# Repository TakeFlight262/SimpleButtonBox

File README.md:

# Simple Button Box

A simple button box, designed for my simracing rig. Includes 9 mechanical key switches and 2 3-way toggle switches.

I've wanted to have a button box for extra inputs on my simracing rig for awhile, so I finally made one!

The box uses 9 mechanical key switches (blue Cherry MX keys) so they feel tactile and satisfying. I also included two three-way toggle switches for additional inputs, totaling to about 13 inputs in total. While it's not a crazy amount, it's enough. The entire box is powered by an Arduino Pro Micro with a USB-C cable connection, making it easy to connect to (instead of micro-USB). I made this project so I could have something useful, but it's also a first for me. I started with a simple project to get the hang of designing projects like this from scratch, so that in the future I can build more complex things (maybe another button box!).
I designed the box to be clean and generic, not to flashy, so it'd fit with any rig and work with any car. I left enough space between buttons for labels and such, but made the buttons big enough so it's easy to press even with gloves in a rig! The buttons being tactile also helps when driving, when you need a sharp, tactile response from the button so you know how many inputs you've pressed.

Features:

* 9x Cherry MX Mechanical Key switches with custom 3D-printed keycaps
* 2x metal 3-way toggle switches (ON-OFF-ON)
* USB-C cable connection
* Removable top cover (for customization, painting, or fixing internal components etc.)
* Horizontal or vertical configuration

Assembly:

The front case is a press fit, and it should have a tight enough tolerance to stay on. If not, you might have to try changing print settings, adding magnets, or gluing (unfortunately). I may add magnets in the future if I find that the friction fit doesn't work well.

For the front cover, you'll notice I have a carbon fiber weave pattern. I printed the front cover on a carbon-fiber weave texture PEI build plate, but you can also wrap it, paint it, or leave it bare if you can't make or don't want the texture.

Buttons are press fit onto the key switches, like normal key caps.

I used mill-max hotswaps, and designed the PCB with that in mind. Solder those on, then add the key switches on top. Ensure that the hotswaps are flush with the board!

Arduino Pro Micro slides in on the BOTTOM, upside down (see above).

Diodes MUST face away from button and towards the row wires, otherwise the matrix will not work.

Switches share ground and solder to pins 9, 10, 14, 15. Change the code if you want to change the input.

If you're printing out the PCB using a 3D printer and soldering + hot gluing the components on like I did, use these wiring diagrams to wire everything up with (ideally) insulated wires. Drill holes to go front/back as needed (I used a solder and burned two holes through, for the row and column wires).

If you're printing/using the PCB:

For soldering order, I soldered the Arduino Pro Micro, then the diodes, then the hotswaps. Then add wires (if you're not using a PCB).

NOTE!!: If you're using the plastic PCB file, you have to be careful about soldering! I solder at 350-400 degrees, the plastic (PLA) will melt almost immediately upon contact with the iron. In order to solder, heat up the METAL component, add solder, then pull away the soldering iron relatively quickly It may take a few tries.

Once everything is soldered, you can slide the PCB onto the mounting pegs in the bottom case. You can add hot glue, superglue, or whatever you need. Just make sure to secure the board.

For the toggle switches, take off the hex nut and washer, slide the switch through the hole, screw on the hex nut and washer (washer on bottom), then turn the switch body while holding the hex nut> Or use a wrench to secure the hex nut. You can do this either vertically or horizontally, depending on how you want to mount the box (so the switches should always be up, but relative to the short side of the box). I mounted the box vertically, so the switches pointed towards/away from the buttons. You can also do it perpendicular (horizontal button box mounting). 

Once the toggle switches are on the lid, solder them to the PCB board.

I mentioned earlier that the lid is press fit. I ended up finding that that did not work! So I drilled two holes on either end. I drove a M2.5 x 8 screw in. It should be a pretty snug fit for the screw. It required a bit of force to screw in. If you want to use magnets or something else, screws are not necessary, but I 100% recommend them.

I also added hot glue around the PCB supports, just to make sure that those fragile supports don't bend or snap when unplugging/plugging the USB-C cable. But again, optional. 

If you find that the buttons don't spring back up, take a pen spring or similar sized springs, use pliers to expand their diameter, then slide them over the 3D printed buttons. I found that it made the buttons feel squishy, so I didn't end up using them> but if you like the added stiffness, then add them. It also might work better with a proper PCB, so I think that is important to note as well.

VERY IMPORTANT: Please be careful when gluing the PCB in, because the USB-C cable might not be able to reach inside if you do it wrong!!

Also note that I did not secure the PCB board, finding that it was ok, but you might need to. The electrical tape I put on the toggle switches ended up being stiff enough to push the board into place, so i found it to be ok. But again, you might need it.

I also found that if the switches are tilted at all and the buttons rub against the lid, you can hold the switch in place until it's straight, then add hot glue to secure it. But again, not sure if you'll need that with a regular PCB.

One FINAL thing: I printed the lid at 100.5%, so I'd recommend doing that, though slightly lower might be ok (my XY compensation was about -2.5mm, so take that into account).

Ok that's all, thanks for reading!

Firmware:

Check "External" folder for libraries, it's important.

Open Arduino IDE, open the sketch, then go to "Sketch>Include Library>Add .ZIP Library" and add the Joystick library.
Select "Tools>Board>Arduino AVR Boards>Arduino Leonardo"
Make sure you select the right COM port, then compile and upload.

If it doesn't upload (like it did for me), try double-clicking reset on the board (or connecting GND and RST twice quickly) right before Arduino IDE uploads.

Credits:

Claude gave me advice for writing firmware
Claude also wrote an upload file to fix an issue on my computer where Arduino wasn't uploading the sketch. I originally included the file in the repo but removed it after further evaluation. Everything currently in the repo is mine.

See "External" folder for all the files, models, and libraries I used!

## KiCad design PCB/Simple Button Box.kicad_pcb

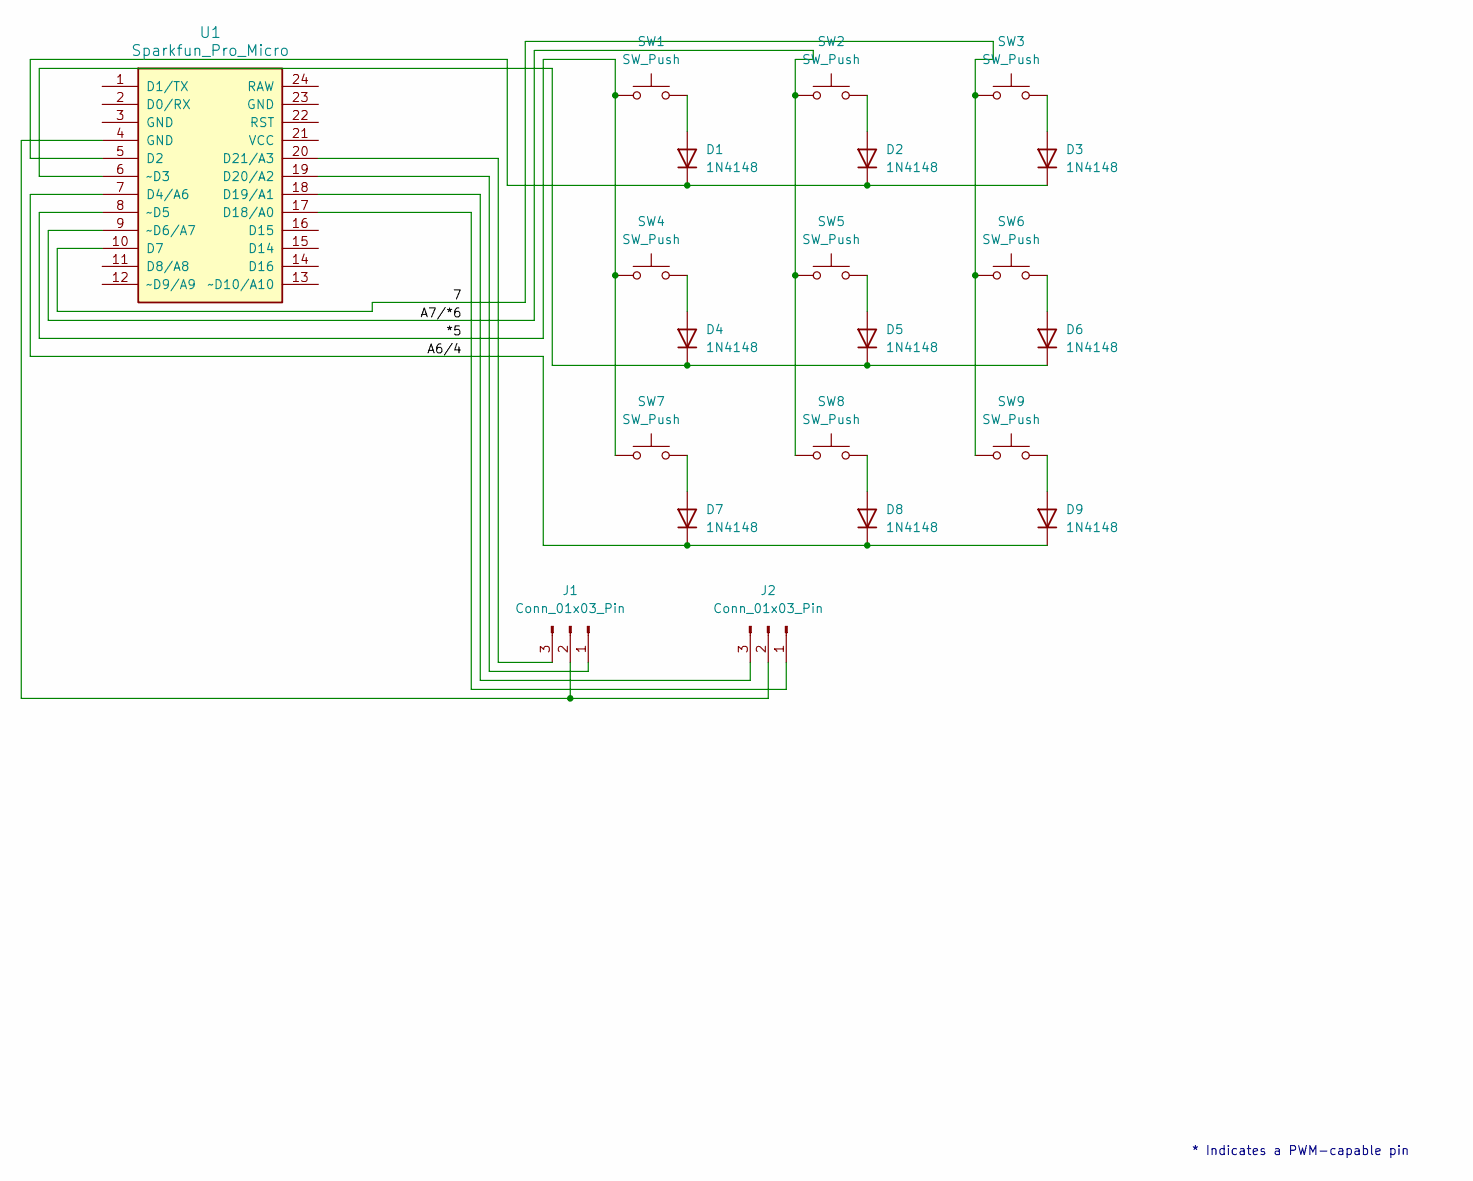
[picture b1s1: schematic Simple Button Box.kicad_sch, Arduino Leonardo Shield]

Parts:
D1, D2, D3, D4, D5, D6, D7, D8, D9: 1N4148; D_DO-35_SOD27_P7.62mm_Horizontal
J1, J2: Conn_01x03_Pin; PinHeader_1x03_P2.54mm_Vertical
SW1, SW2, SW3, SW4, SW5, SW6, SW7, SW8, SW9: SW_Push; SW_Cherry_MX_1.00u_Plate
U1: Sparkfun_Pro_Micro

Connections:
/7: SW3.1, SW6.1, SW9.1, U1.10 (D7)
/*5: SW1.1, SW4.1, SW7.1, U1.8 (~D5)
/A6/4: D7.1 (K), D8.1 (K), D9.1 (K), U1.7 (D4/A6)
/A7/*6: SW2.1, SW5.1, SW8.1, U1.9 (~D6/A7)
unnamed: D1.2 (A), SW1.2
unnamed: D1.1 (K), D2.1 (K), D3.1 (K), U1.5 (D2)
unnamed: D2.2 (A), SW2.2
unnamed: D3.2 (A), SW3.2
unnamed: D4.2 (A), SW4.2
unnamed: D4.1 (K), D5.1 (K), D6.1 (K), U1.6 (~D3)
unnamed: D5.2 (A), SW5.2
unnamed: D6.2 (A), SW6.2
unnamed: D7.2 (A), SW7.2
unnamed: D8.2 (A), SW8.2
unnamed: D9.2 (A), SW9.2
unnamed: J1.1, U1.19 (D20/A2)
unnamed: J1.2, J2.2, U1.4 (GND)
unnamed: J1.3, U1.20 (D21/A3)
unnamed: J2.1, U1.17 (D18/A0)
unnamed: J2.3, U1.18 (D19/A1)

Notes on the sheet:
* Indicates a PWM-capable pin

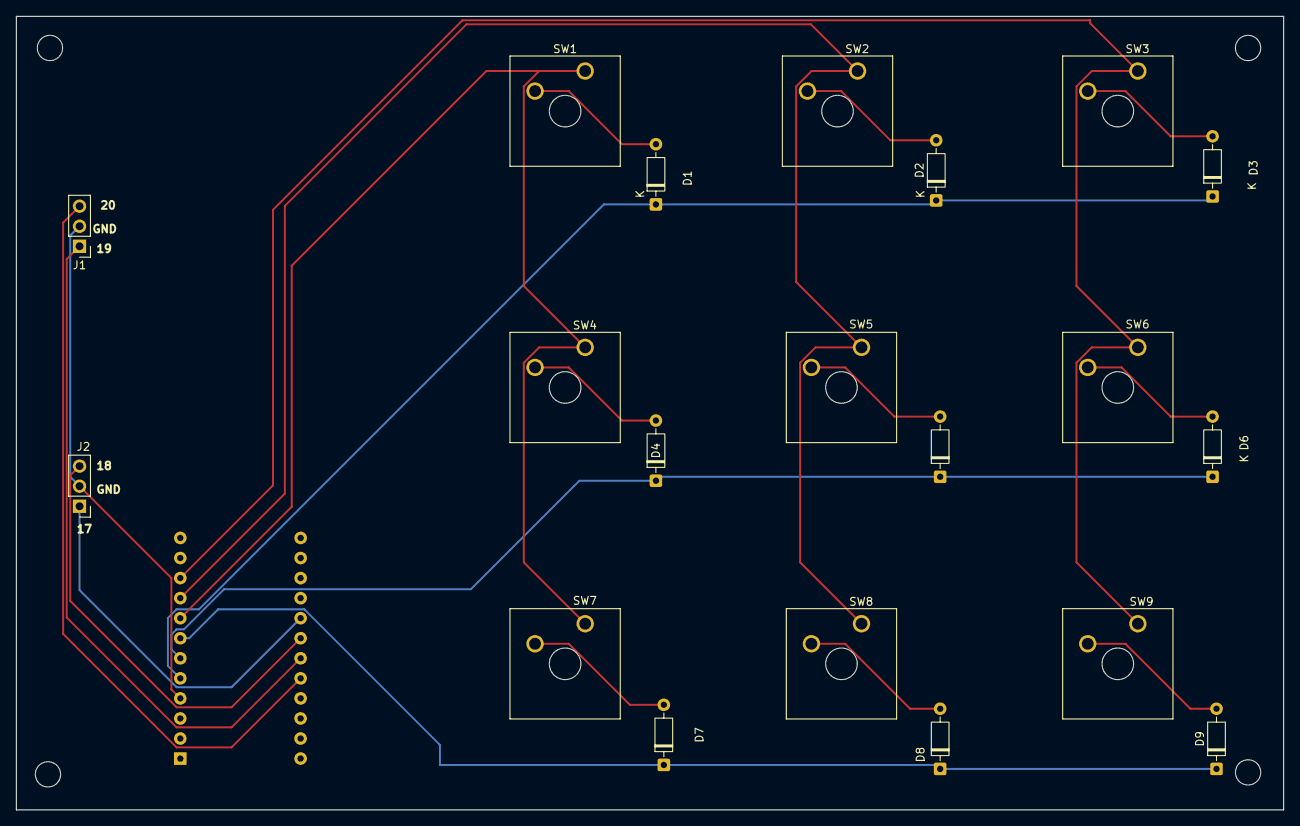
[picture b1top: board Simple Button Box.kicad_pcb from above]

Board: 2 copper layers, 160.5 x 100.5 mm, 21 parts (1 on the bottom side), 20 nets.
